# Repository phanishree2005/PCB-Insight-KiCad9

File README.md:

# PCB INSIGHT 🔍⚡
### Intelligent PCB Design Analysis, Connectivity Auditing, and Engineering Report Generation for KiCad 9

---

## 📌 Executive Overview
**PCB Insight** is an intelligent, modular, and explainable PCB design analysis utility designed specifically for **KiCad 9**. It bridges Computer Science (modular software design, rule engines, graph models, typed dataclasses) with Electronics Design Automation (pad-to-net topology, Bill of Materials hygiene, footprint validation, and Design for Manufacturing checks).

Developed for the **FOSSEE eSim Semester Long Internship – Autumn 2026 (Screening Task 6)**, PCB Insight inspects printed circuit board designs, identifies subtle electrical and metadata anomalies, and synthesizes standalone, interactive engineering reports.

---

## 🚀 Key Features

| Capability | Engineering Focus | Technical Description |
| :--- | :--- | :--- |
| **KiCad 9 IPC Integration** | Modern Out-of-Process Architecture | Directly connects to KiCad 9's official IPC API (`kicad-python`) via Protocol Buffers and Nanomsg-NG named pipes / sockets. |
| **Legacy pcbnew Fallback** | Maximum Compatibility | Seamless fallback to in-process `pcbnew.ActionPlugin` for classic toolbar execution in existing KiCad installations. |
| **Component Health Audit** | Bill of Materials (BOM) Hygiene | Evaluates component references against IEEE Std 315/200; detects duplicates, missing values (`~`), placeholder designators (`R?`), and unassigned footprints. |
| **Connectivity Graph Engine** | Electrical Sanity & Antenna Detection | Builds a complete net-to-pad topological index; detects dangling single-pin nets (RF stubs), unassigned active pads, and differentiates mechanical mounting holes (NPTH). |
| **Explainable Rule Engine** | Deterministic Quality Verification | Modular rule architecture where every reported finding includes a unique Rule ID, severity classification, affected components/nets, technical rationale, and remediation steps. |
| **Native KiCad DRC Traceability**| Authoritative Validation | Safely invokes `kicad-cli pcb drc --format json` when available to incorporate native DRC violations without duplicating clearance solvers. |
| **Air-Gapped HTML & CSV Reports**| Zero-Network Data Security | Generates single-file, responsive, print-friendly HTML reports with search/filtering, plus RFC 4180 CSV exports of component inventories and findings. |
| **Offline S-Expression Engine** | Headless Testing & CI/CD | Pure-Python recursive S-expression parser for `.kicad_pcb` files allowing 100% headless testing without requiring a live KiCad GUI session. |

---

## 🏗 System Architecture

PCB Insight follows a **Hexagonal (Ports-and-Adapters) Clean Architecture**:

```
+-----------------------------------------------------------+
|                   External KiCad Sources                  |
|  [KiCad 9 IPC API]   [Legacy pcbnew]   [.kicad_pcb File]  |
+-----------------------------------------------------------+
                              |
                   [BoardAdapter Interface]
                              v
+-----------------------------------------------------------+
|               Normalized Data Models (Core)               |
|      BoardData, ComponentData, NetData, PadData, etc.     |
+-----------------------------------------------------------+
                              |
          +-------------------+-------------------+
          v                                       v
+-----------------------+               +-------------------+
|  Analysis & Rules     |               | Reporting Engine  |
| - Component Analyzer  |               | - Standalone HTML |
| - Net Connectivity    |               | - CSV Exporter    |
| - Design Quality Rules|               | - Summary Cards   |
+-----------------------+               +-------------------+
```

Full details are documented in [docs/ARCHITECTURE.md](docs/ARCHITECTURE.md) and [docs/DESIGN_DOCUMENT.md](docs/DESIGN_DOCUMENT.md).

---

## 📚 Technical Documentation Suite

The repository contains comprehensive engineering documentation:
- 📖 **[Design Document (27 Sections)](docs/DESIGN_DOCUMENT.md):** Complete technical specifications, algorithms, diagrams, and methodologies.
- 🏛 **[System Architecture](docs/ARCHITECTURE.md):** Architectural patterns, data models, and sequence flows.
- ⚖️ **[Technical Decisions (ADRs)](docs/TECHNICAL_DECISIONS.md):** Justification for IPC API selection, fallbacks, and design trade-offs.
- 🔌 **[API Integration Guide](docs/API_INTEGRATION.md):** Deep comparison of KiCad 9 IPC API vs. legacy `pcbnew` SWIG bindings.
- ⚡ **[Electronics Concepts](docs/ELECTRONICS_CONCEPTS.md):** Reference designators, pad types, net topology, and RF stub physics.
- 🧪 **[Testing Strategy](docs/TESTING.md):** Test execution matrix, clean and faulty fixture specifications.
- ⚠️ **[Technical Limitations](docs/LIMITATIONS.md):** Documented boundaries and operational scope.
- ✅ **[FOSSEE Submission Checklist](docs/FOSSEE_SUBMISSION_CHECKLIST.md):** Direct mapping of internship criteria to implementation modules.

---

## 💻 Installation & Quick Start

Refer to [INSTALLATION.md](INSTALLATION.md) for complete multi-platform setup instructions.

```bash
# 1. Clone repository
git clone https://github.com/username/PCB-Insight-KiCad9-Plugin.git
cd PCB-Insight-KiCad9-Plugin

# 2. Install dependencies
pip install -r requirements.txt

# 3. Run automated test suite
pytest tests/ -v
```

---

## 📜 License
This project is licensed under the MIT License - see the [LICENSE](LICENSE) file for details.

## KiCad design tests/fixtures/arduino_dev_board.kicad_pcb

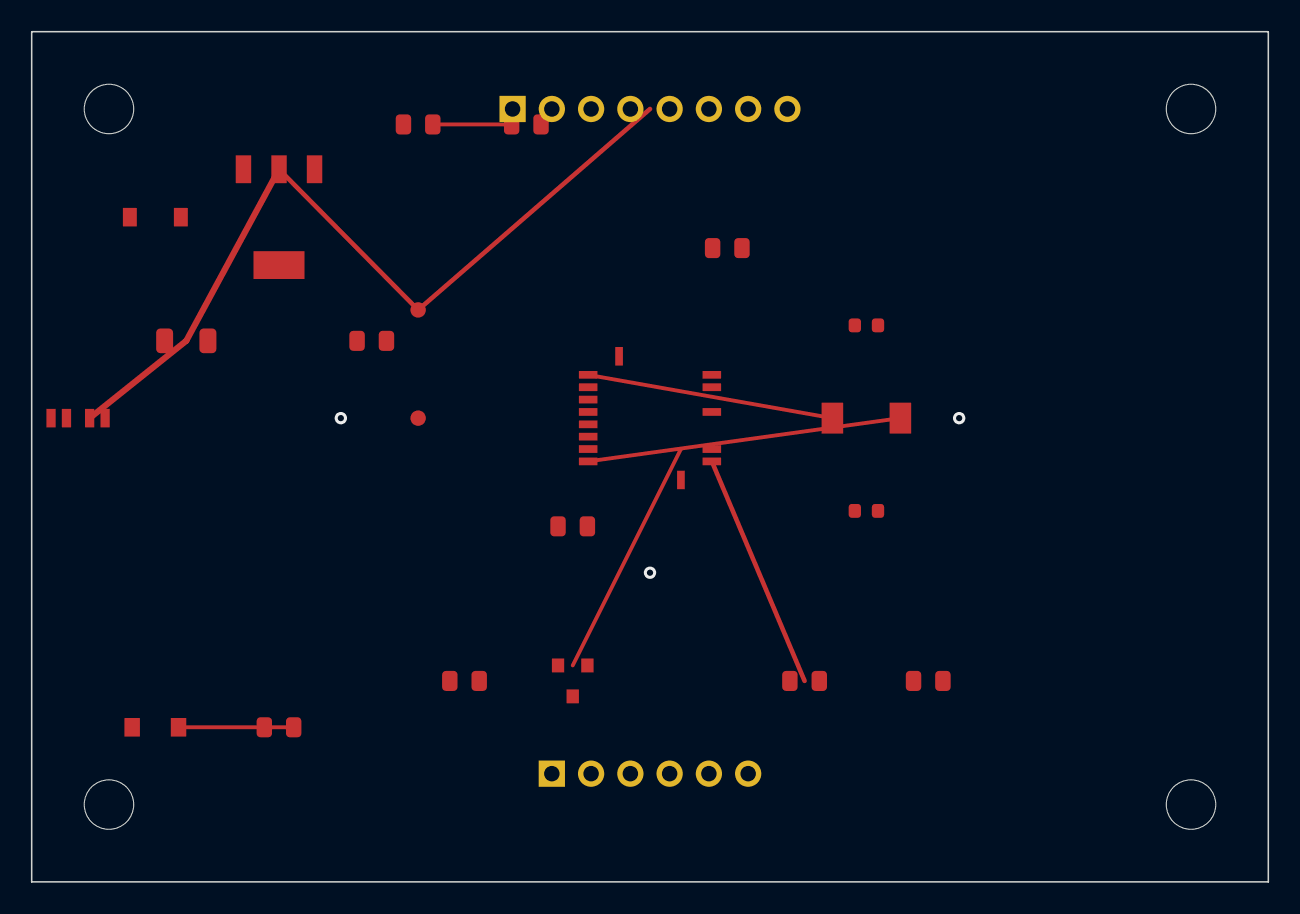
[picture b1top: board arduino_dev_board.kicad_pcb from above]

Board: 2 copper layers, 80.0 x 55.0 mm, 27 parts (0 on the bottom side), 13 nets.

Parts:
C1: 10uF; C_1206_3216Metric
C2, C3, C4: 100nF; C_0805_2012Metric
C5, C6: 22pF; C_0603_1608Metric
D1: PWR_GREEN; LED_0805_2012Metric
D2: STAT_BLUE; LED_0805_2012Metric
D3: 1N4148W; D_SOD-123
H1, H2, H3, H4: MountingHole; MountingHole_3.2mm_M3
J1: USB-C; USB_C_Receptacle_HRO_TYPE-C-31-M-12
J2: Digital_IO; PinHeader_1x08_P2.54mm_Vertical
J3: Analog_In; PinHeader_1x06_P2.54mm_Vertical
Q1: 2N7002; SOT-23
R1: 10k; R_0805_2012Metric
R2, R3: 1k; R_0805_2012Metric
R4: 100k; R_0805_2012Metric
SW1: RESET_BTN; SW_Push_SPST_NO_Alps_SKRK
TP1: TP_3V3; TestPoint_Pad_D1.0mm
TP2: TP_GND; TestPoint_Pad_D1.0mm
U1: ATmega328P-AU; TQFP-32_7x7mm_P0.8mm
U2: AMS1117-3.3; SOT-223-3_TabPin2
Y1: 16MHz; Crystal_SMD_5032-2Pin_5.0x3.2mm

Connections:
+3V3: C2.1, J2.5, J3.6, TP1.1, U2.2, U2.4
+5V: C1.1, C3.1, C4.1, D3.1, D3.2, J1.A4, J1.B4, J2.4, J3.5, R1.1, R2.1, R3.2, U1.4, U1.6, U1.18, U2.3
A0: J3.1, U1.23
A1: J3.2, U1.24
CTRL_GATE: J2.7, Q1.1, R4.1, U1.15
D0_RX: J2.1, U1.1
D1_TX: J2.2, U1.2
D13_LED: D2.2, J2.8, Q1.3, R3.1, U1.17
GND: C1.2, C2.2, C3.2, C4.2, C5.2, C6.2, D1.1, D2.1, J1.A1, J1.B1, J2.3, J3.3, J3.4, Q1.2, R4.2, SW1.2, TP2.1, U1.3, U1.5, U1.21, U2.1
PWR_IND: D1.2, R2.2
RESET: J2.6, R1.2, SW1.1, U1.29
XTAL1: C5.1, U1.7, Y1.1
XTAL2: C6.1, U1.8, Y1.2

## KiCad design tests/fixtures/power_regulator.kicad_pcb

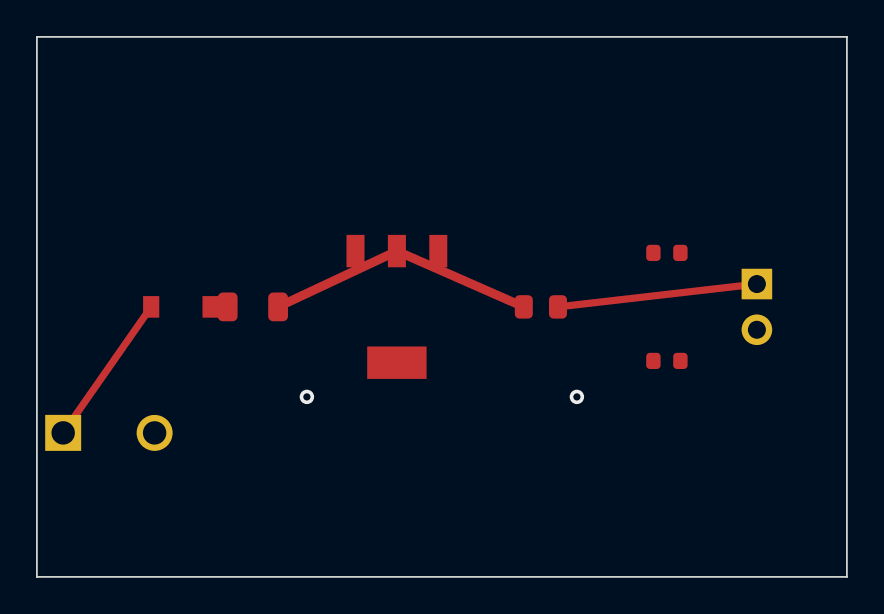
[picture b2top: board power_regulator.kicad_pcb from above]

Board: 2 copper layers, 45.0 x 30.0 mm, 8 parts (0 on the bottom side), 5 nets.

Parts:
C1: 10uF; C_1206_3216Metric
C2: 22uF; C_0805_2012Metric
D1: B5819W; D_SOD-123
D2: GREEN; LED_0603_1608Metric
J1: Input_Power; TerminalBlock_bornier-2_P5.08mm
J2: Output_3V3; PinHeader_1x02_P2.54mm_Vertical
R1: 1k; R_0603_1608Metric
U1: AMS1117-3.3; SOT-223-3_TabPin2

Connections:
+3V3: C2.1, J2.1, R1.1, U1.2, U1.4
GND: C1.2, C2.2, D2.1, J1.2, J2.2, U1.1
unnamed: D2.2, R1.2
VIN: C1.1, D1.1, U1.3
VRAW: D1.2, J1.1

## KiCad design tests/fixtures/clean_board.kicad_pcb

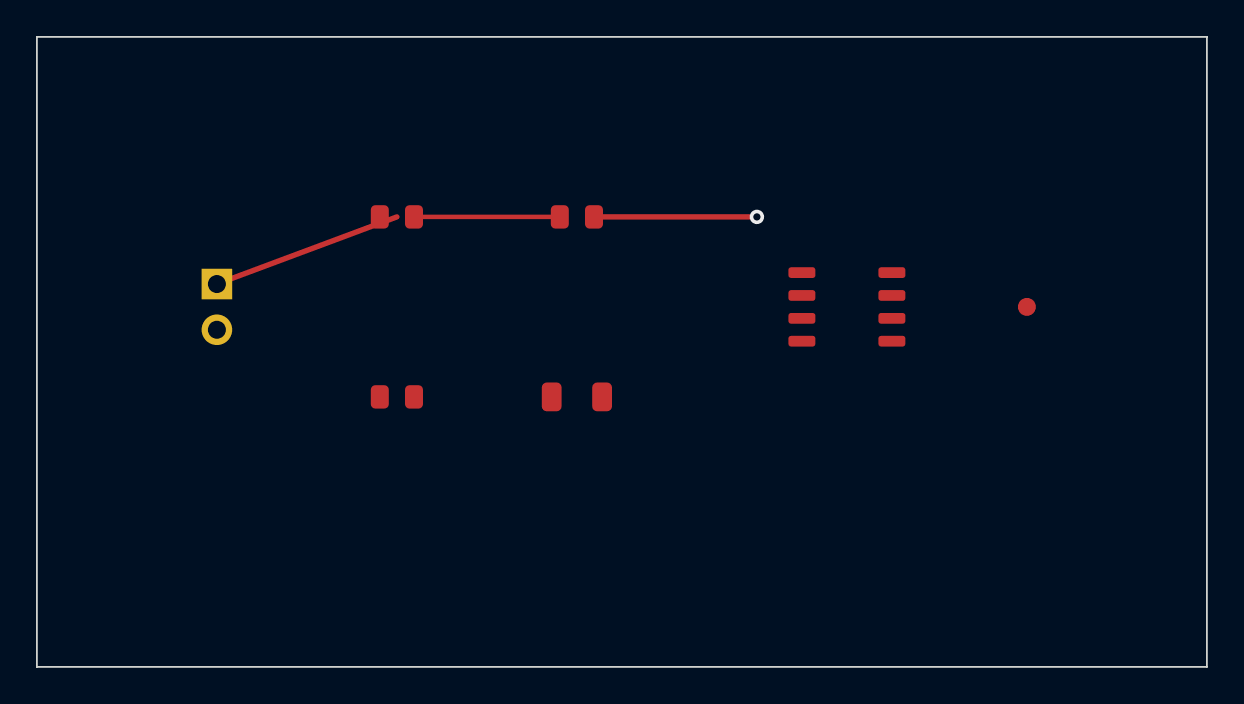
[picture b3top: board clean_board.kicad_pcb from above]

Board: 2 copper layers, 65.0 x 35.0 mm, 7 parts (0 on the bottom side), 4 nets.

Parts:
C1: 100nF; C_0805_2012Metric
C2: 10uF; C_1206_3216Metric
J1: Power_In; PinHeader_1x02_P2.54mm_Vertical
R1: 10k; R_0805_2012Metric
R2: 4.7k; R_0805_2012Metric
TP1: TestPoint; TestPoint_Pad_D1.0mm
U1: NE555P; SOIC-8_3.9x4.9mm_P1.27mm

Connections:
+5V: C1.1, C2.1, J1.1, R1.1, U1.4, U1.8
GND: C1.2, C2.2, J1.2, R2.2, U1.1, U1.5
unnamed: R1.2, R2.1, U1.2, U1.6, U1.7
OUT: TP1.1, U1.3

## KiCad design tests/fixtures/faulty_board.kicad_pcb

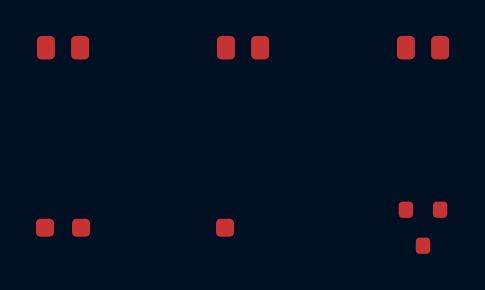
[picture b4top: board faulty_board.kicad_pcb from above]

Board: 2 copper layers, 6 parts (0 on the bottom side), 2 nets, no tracks yet.

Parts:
C1: 100nF; C_0805_2012Metric
C1#2: 220nF; C_0805_2012Metric
D1: D_SOD-123
Q1: 2N3904; SOT-23
R?: 10k; R_0805_2012Metric
U2: ATTINY85

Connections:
+5V: C1.1, C1#2.1, D1.1, Q1.2, R?.1, U2.1
GND: C1.2, C1#2.2, D1.2, Q1.1

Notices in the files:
README.md:
License: MIT
